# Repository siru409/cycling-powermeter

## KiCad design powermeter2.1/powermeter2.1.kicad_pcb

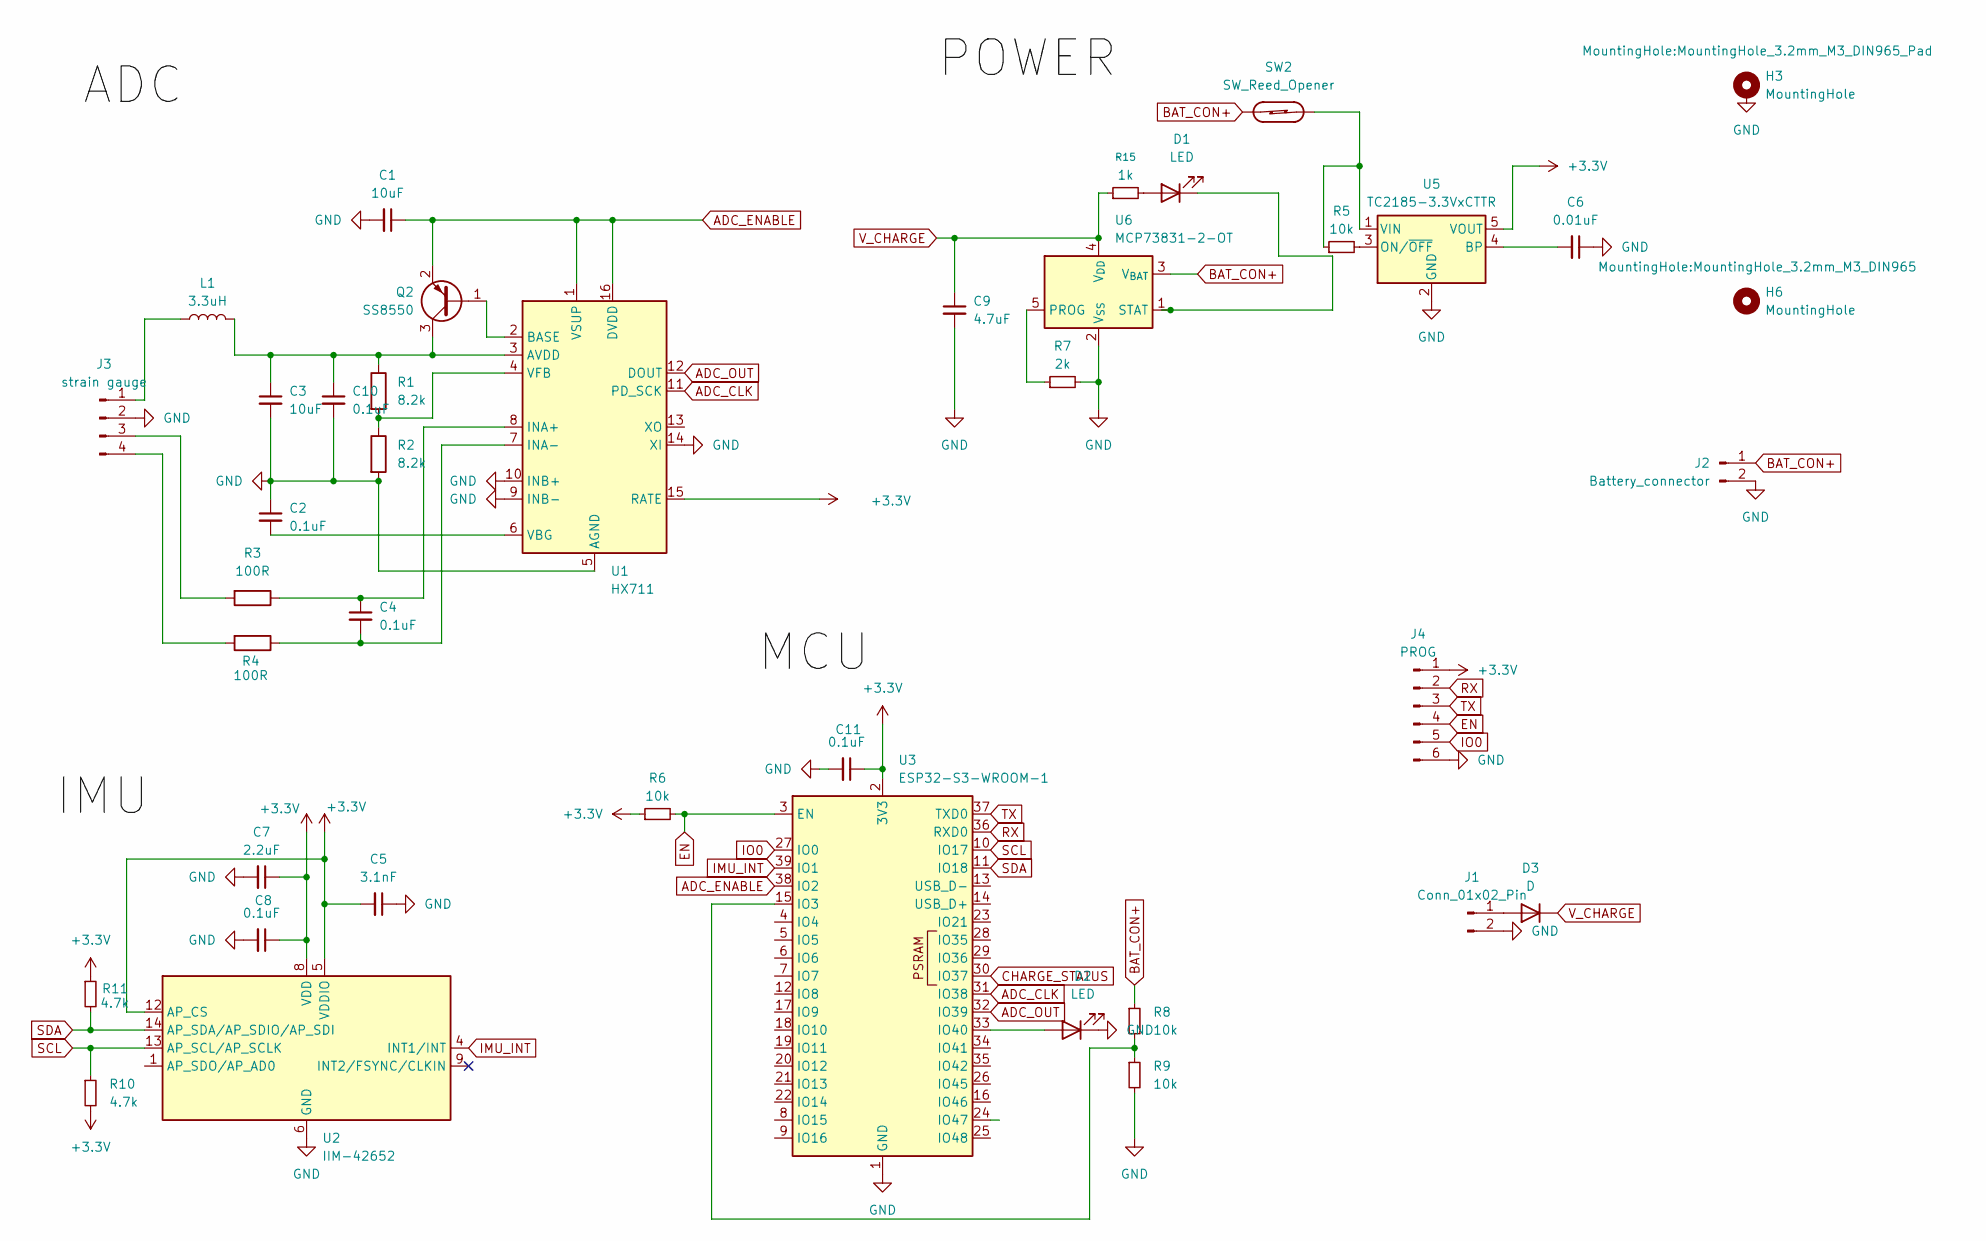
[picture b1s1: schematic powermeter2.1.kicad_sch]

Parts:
C1, C3: 10uF; C_0603_1608Metric
C2, C4, C8, C10, C11: 0.1uF; C_0603_1608Metric
C5: 3.1nF; C_0603_1608Metric
C6: 0.01uF; C_0603_1608Metric
C7: 2.2uF; C_0603_1608Metric
C9: 4.7uF; C_0603_1608Metric
D1, D2: LED; LED_0603_1608Metric_Pad1.05x0.95mm_HandSolder
D3: D; D_0603_1608Metric
H3: MountingHole; MountingHole_3.2mm_M3_DIN965_Pad
H6: MountingHole; MountingHole_3.2mm_M3_DIN965
J1: Conn_01x02_Pin; PinHeader_1x02_P2.54mm_Vertical
J2: Battery_connector; R_Axial_DIN0204_L3.6mm_D1.6mm_P1.90mm_Vertical
J3: strain gauge; PinHeader_1x04_P2.54mm_Vertical
J4: PROG; PinHeader_2x03_P1.27mm_Vertical
L1: 3.3uH; L_0603_1608Metric
Q2: SS8550; SOT-23
R1, R2: 8.2k; R_0603_1608Metric
R3, R4: 100R; R_0603_1608Metric
R5, R6, R8, R9: 10k; R_0603_1608Metric
R7: 2k; R_0603_1608Metric
R10, R11: 4.7k; R_0603_1608Metric
R15: 1k; R_0603_1608Metric
SW2: SW_Reed_Opener; SW_SPST_REED_CT05-XXXX-G1
U1: HX711; SOP-16_3.9x9.9mm_P1.27mm
U2: IIM-42652; Bosch_LGA-14_3x2.5mm_P0.5mm
U3: ESP32-S3-WROOM-1
U5: TC2185-3.3VxCTTR; SOT-23-5
U6: MCP73831-2-OT; SOT-23-5

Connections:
+3.3V: C5.2, C7.1, C8.1, C11.1, J4.1, R6.1, R10.2, R11.1, U1.15 (RATE), U2.5 (VDDIO), U2.8 (VDD), U2.12 (AP_CS), U3.2 (3V3), U5.5 (VOUT)
ADC_CLK: U1.11 (PD_SCK), U3.31 (IO38)
ADC_ENABLE: C1.1, Q2.2 (E), U1.1 (VSUP), U1.16 (DVDD), U3.38 (IO2)
ADC_OUT: U1.12 (DOUT), U3.32 (IO39)
BAT_CON+: J2.1, R8.1, SW2.1, U6.3 (V_{BAT})
CHARGE_STATUS: U3.30 (IO37)
EN: J4.4, R6.2, U3.3 (EN)
GND: C1.2, C2.1, C3.2, C5.1, C6.1, C7.2, C8.2, C9.2, C10.2, C11.2, D2.1 (K), J1.2, J2.2, J3.2, J4.6, R2.2, R7.2, R9.2, U1.5 (AGND), U1.9 (INB-), U1.10 (INB+), U1.14 (XI), U2.6 (GND), U2.7 (GND), U3.1 (GND), U3.40 (GND), U3.41 (GND), U5.2 (GND), U6.2 (V_{SS})
IMU_INT: U2.4 (INT1/INT), U3.39 (IO1)
IO0: J4.5, U3.27 (IO0)
unnamed: D1.2 (A), R15.2
unnamed: D1.1 (K), U6.1 (STAT)
unnamed: D2.2 (A), U3.33 (IO40)
unnamed: D3.2 (A), J1.1
unnamed: J3.1, L1.1
unnamed: J3.3, R3.2
unnamed: J3.4, R4.2
unnamed: Q2.1 (B), U1.2 (BASE)
unnamed: C3.1, C10.1, L1.2, Q2.3 (C), R1.1, U1.3 (AVDD)
unnamed: C4.1, R3.1, U1.8 (INA+)
unnamed: C4.2, R4.1, U1.7 (INA-)
unnamed: C2.2, U1.6 (VBG)
unnamed: R1.2, R2.1, U1.4 (VFB)
unnamed: R8.2, R9.1, U3.15 (IO3)
unnamed: C6.2, U5.4 (BP)
unnamed: R5.2, U5.3 (ON/~OFF)
unnamed: R5.1, SW2.2, U5.1 (VIN)
unnamed: R7.1, U6.5 (PROG)
RX: J4.2, U3.36 (RXD0)
SCL: R10.1, U2.13 (AP_SCL/AP_SCLK), U3.10 (IO17)
SDA: R11.2, U2.14 (AP_SDA/AP_SDIO/AP_SDI), U3.11 (IO18)
TX: J4.3, U3.37 (TXD0)
V_CHARGE: C9.1, D3.1 (K), R15.1, U6.4 (V_{DD})

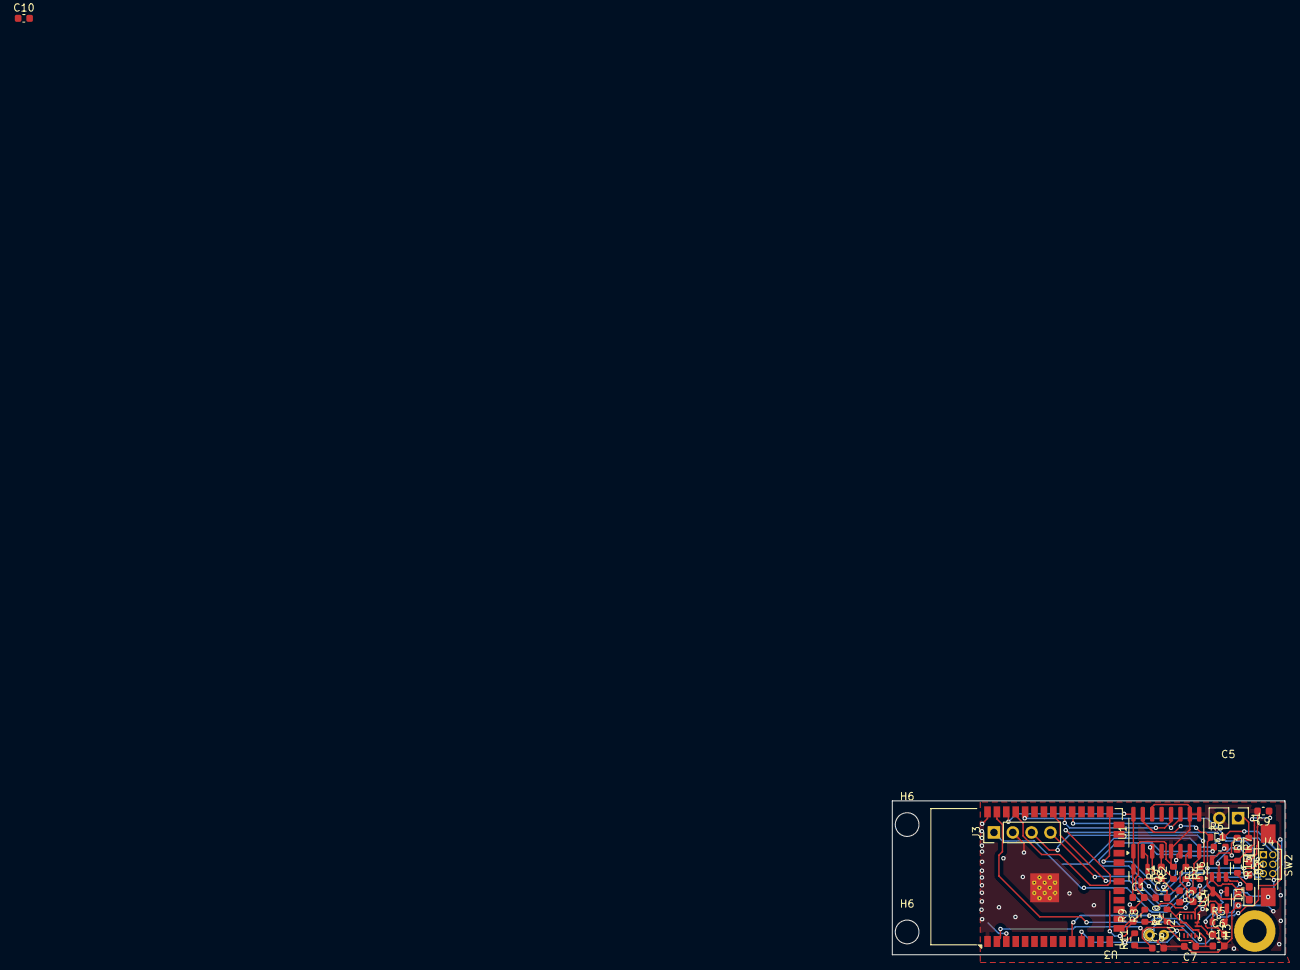
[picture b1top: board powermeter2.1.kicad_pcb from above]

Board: 2 copper layers, 53.0 x 20.8 mm, 41 parts (0 on the bottom side), 32 nets.

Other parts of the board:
H6#2: MountingHole; MountingHole_3.2mm_M3_DIN965

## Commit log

2025-08-14 upload
